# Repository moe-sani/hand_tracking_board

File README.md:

# hand_tracking_board

    branch name: backup_8_core_board
    hardware version: 
    Processor: Arduino 

* author: Mohammad Fattahi Sani
* Email: fattahi.m91@gmail.com

----------

This is the old board used to collect data using logic analyzer.

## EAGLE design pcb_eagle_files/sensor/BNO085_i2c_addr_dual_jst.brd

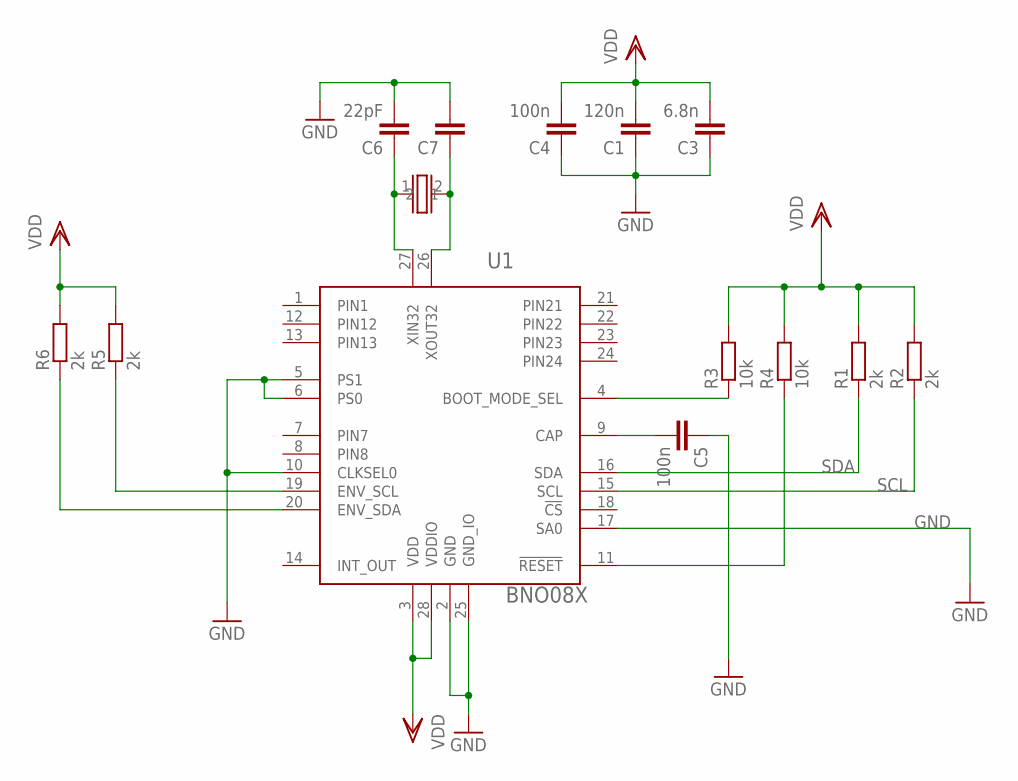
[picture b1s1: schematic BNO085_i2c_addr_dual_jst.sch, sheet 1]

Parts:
C1: 120n; C0402
C3: 6.8n; C0402
C4, C5: 100n; C0402
C6: 22pF; C0402
C7: C-EUC0402; C0402
R1, R2, R5, R6: 2k; R0402
R3, R4: 10k; R0402
U1: BNO08X; LGA-28_3.80X5.20/0.5
U$1: ABS05

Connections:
GND: C1.1, C3.1, C4.1, C5.1, C6.2, C7.2, U1.2 (GND), U1.5 (PS1), U1.6 (PS0), U1.10 (CLKSEL0), U1.17 (SA0), U1.25 (GND_IO); also elsewhere on the board
unnamed: C6.1, U1.27 (XIN32), U$1.1
unnamed: C7.1, U1.26 (XOUT32), U$1.2
unnamed: C5.2, U1.9 (CAP)
unnamed: R3.1, U1.4 (BOOT_MODE_SEL)
unnamed: R5.1, U1.19 (ENV_SCL)
unnamed: R4.1, U1.11 (!RESET)
unnamed: R6.1, U1.20 (ENV_SDA)
SCL: R2.1, U1.15 (SCL); also elsewhere on the board
SDA: R1.1, U1.16 (SDA); also elsewhere on the board
VDD: C1.2, C3.2, C4.2, R1.2, R2.2, R3.2, R4.2, R5.2, R6.2, U1.3 (VDD), U1.28 (VDDIO); also elsewhere on the board

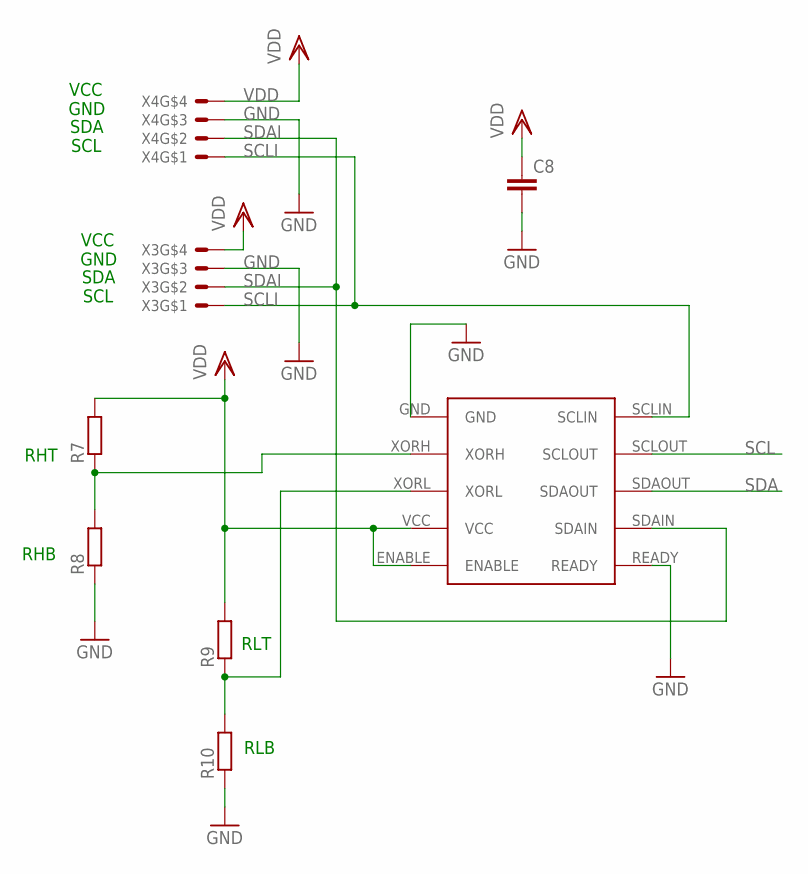
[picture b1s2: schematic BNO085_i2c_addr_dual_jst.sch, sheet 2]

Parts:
C8: C-EUC0402; C0402
R7, R8, R9, R10: R-EU_R0402; R0402
U$3: LIC4316; DD-DFN-10
X3, X4: SM04B-XSRS; SM04B-XSRS-ETB

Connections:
GND: C8.2, R8.1, R10.1, U$3.GND, U$3.READY, X3.3, X4.3; also elsewhere on the board
unnamed: R7.1, R8.2, U$3.XORH
unnamed: R9.1, R10.2, U$3.XORL
SCL: U$3.SCLOUT; also elsewhere on the board
SCLI: U$3.SCLIN, X3.1, X4.1
SDA: U$3.SDAOUT; also elsewhere on the board
SDAI: U$3.SDAIN, X3.2, X4.2
VDD: C8.1, R7.2, R9.2, U$3.ENABLE, U$3.VCC, X3.4, X4.4; also elsewhere on the board

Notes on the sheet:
SCL
SDA
VCC
GND
RHT
RHB
RLT
RLB

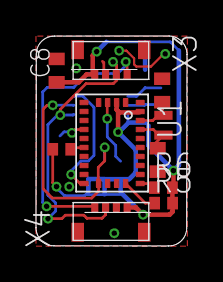
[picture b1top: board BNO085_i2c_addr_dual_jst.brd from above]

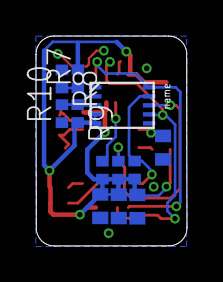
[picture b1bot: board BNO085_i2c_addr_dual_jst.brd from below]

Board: 2 copper layers, 8.4 x 11.7 mm, 24 parts (12 on the bottom side), 15 nets.

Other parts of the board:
LOGO3: OSHW-LOGOS; OSHW-LOGO-S
U$2: BQ_LOGO_MEDIUM

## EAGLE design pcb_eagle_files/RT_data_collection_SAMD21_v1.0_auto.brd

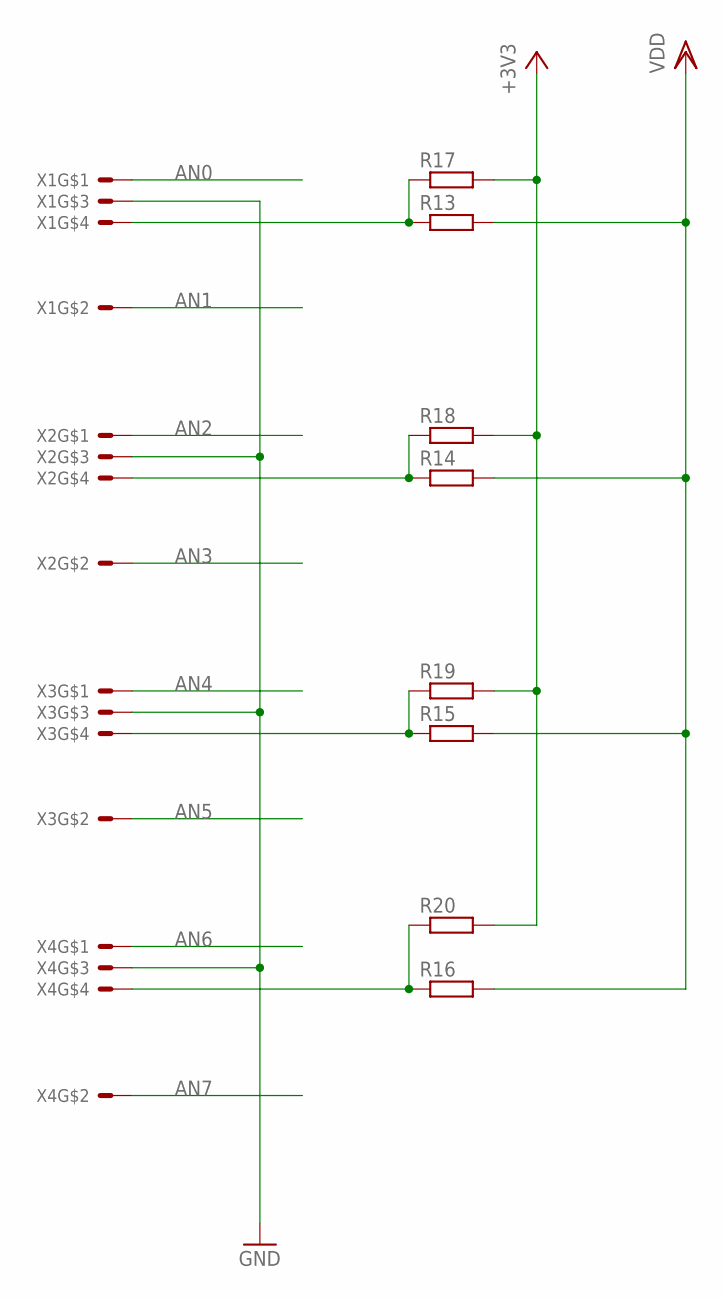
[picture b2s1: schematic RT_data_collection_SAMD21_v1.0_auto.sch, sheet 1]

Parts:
R13, R14, R15, R16, R17, R18, R19, R20: R-EU_R0201; R0201
X1, X3: CON-JST2_SM04B-XSRS; CON-JST2_SM04B-XSRS-ETB
X2, X4: SM04B-XSRS; SM04B-XSRS-ETB

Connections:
+3V3: R17.2, R18.2, R19.2, R20.2; also elsewhere on the board
AN0: X1.1; also elsewhere on the board
AN1: X1.2; also elsewhere on the board
AN2: X2.1; also elsewhere on the board
AN3: X2.2; also elsewhere on the board
AN4: X3.1; also elsewhere on the board
AN5: X3.2; also elsewhere on the board
AN6: X4.1; also elsewhere on the board
AN7: X4.2; also elsewhere on the board
GND: X1.3, X2.3, X3.3, X4.3; also elsewhere on the board
unnamed: R16.1, R20.1, X4.4
unnamed: R14.1, R18.1, X2.4
unnamed: R15.1, R19.1, X3.4
unnamed: R13.1, R17.1, X1.4
VDD: R13.2, R14.2, R15.2, R16.2; also elsewhere on the board

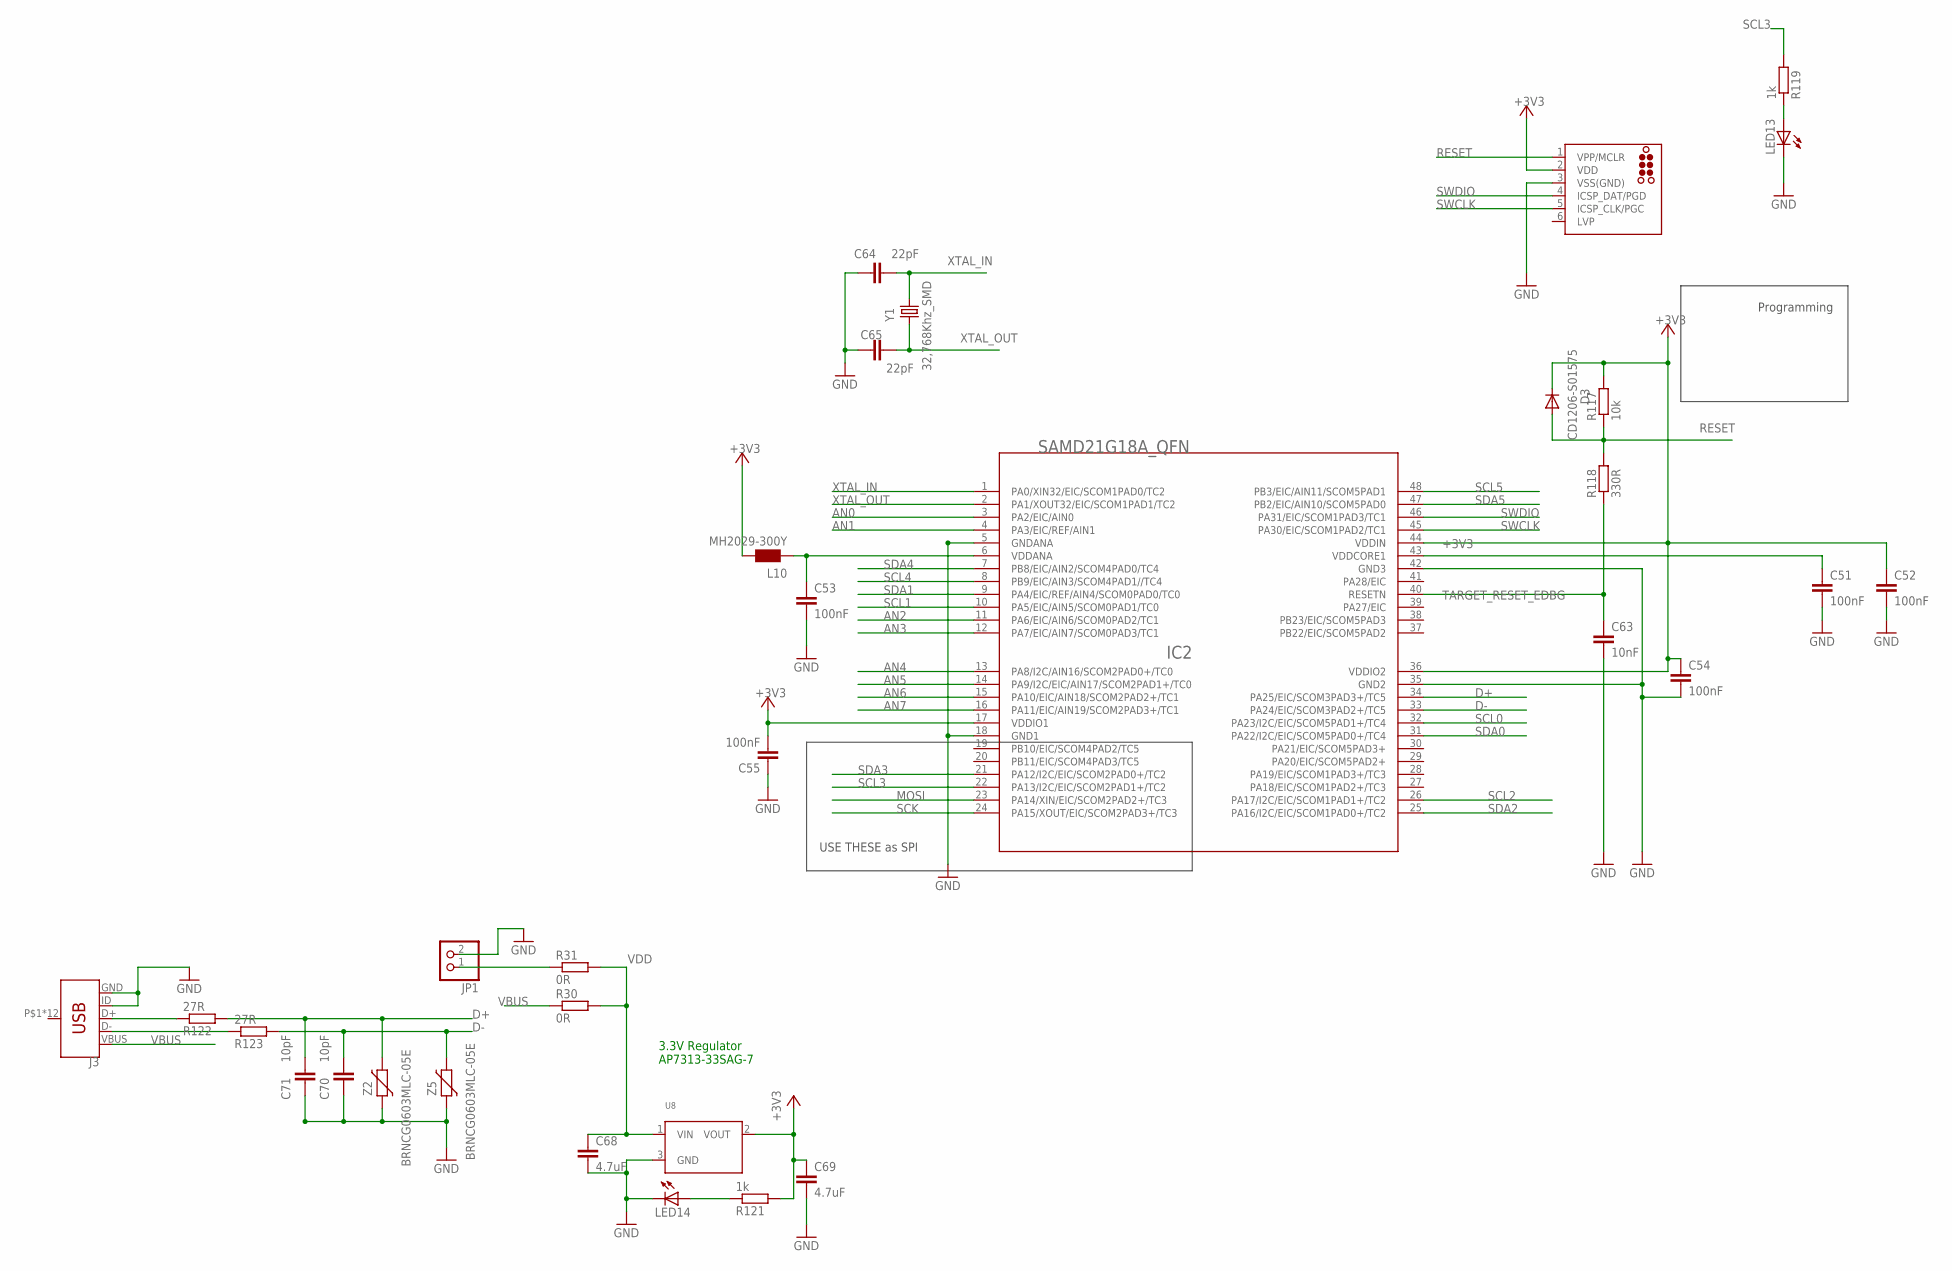
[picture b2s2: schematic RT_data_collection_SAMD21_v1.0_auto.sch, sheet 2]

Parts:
C51, C52, C53, C54, C55: 100nF; C0402
C63: 10nF; C0402
C64, C65: 22pF; C0402
C68, C69: 4.7uF; C0603
C70, C71: 10pF; C0402
D3: CD1206-S01575; MINIMELF
IC2: SAMD21G18A_QFN
J2: TC2030-MCP-NL
J3: USB_MICRO-B; USB-MICROB-PTH-WIDE
JP1: PINHD-1X2; 1X02
L10: MH2029-300Y; 0805
LED13, LED14: LEDCHIPLED_0805; CHIPLED_0805
R30, R31: 0R; R0603
R117: 10k; R0402
R118: 330R; R0402
R119, R121: 1k; R0402
R122, R123: 27R; R0402
U8: VREG_SOT23; SOT23-R
Y1: 32,768Khz_SMD; CRISTALLI_RESONATOR_EPSON_FC_145
Z2, Z5: BRNCG0603MLC-05E; CT/CN0603

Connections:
+3V3: C52.1, C54.1, C55.2, C69.1, D3.C, IC2.17 (VDDIO1), IC2.36 (VDDIO2), IC2.44 (VDDIN), J2.2 (VDD), L10.2, R117.2, R121.2, U8.2 (VOUT); also elsewhere on the board
AN0: IC2.3 (PA2/EIC/AIN0); also elsewhere on the board
AN1: IC2.4 (PA3/EIC/REF/AIN1); also elsewhere on the board
AN2: IC2.11 (PA6/EIC/AIN6/SCOM0PAD2/TC1); also elsewhere on the board
AN3: IC2.12 (PA7/EIC/AIN7/SCOM0PAD3/TC1); also elsewhere on the board
AN4: IC2.13 (PA8/I2C/AIN16/SCOM2PAD0+/TC0); also elsewhere on the board
AN5: IC2.14 (PA9/I2C/EIC/AIN17/SCOM2PAD1+/TC0); also elsewhere on the board
AN6: IC2.15 (PA10/EIC/AIN18/SCOM2PAD2+/TC1); also elsewhere on the board
AN7: IC2.16 (PA11/EIC/AIN19/SCOM2PAD3+/TC1); also elsewhere on the board
D+: C71.2, IC2.34 (PA25/EIC/SCOM3PAD3+/TC5), R122.2, Z2.2
D-: C70.2, IC2.33 (PA24/EIC/SCOM3PAD2+/TC5), R123.2, Z5.2
GND: C51.2, C52.2, C53.2, C54.2, C55.1, C63.2, C64.1, C65.1, C68.2, C69.2, C70.1, C71.1, IC2.5 (GNDANA), IC2.18 (GND1), IC2.35 (GND2), IC2.42 (GND3), J2.3 (VSS(GND)), J3.GND, J3.ID, JP1.2, LED13.C, LED14.C, U8.3 (GND), Z2.1, Z5.1; also elsewhere on the board
MOSI: IC2.23 (PA14/XIN/EIC/SCOM2PAD2+/TC3)
unnamed: J3.D+, R122.1
unnamed: J3.D-, R123.1
unnamed: C51.1, IC2.43 (VDDCORE1)
unnamed: JP1.1, R31.1
unnamed: C53.1, IC2.6 (VDDANA), L10.1
unnamed: LED13.A, R119.1
unnamed: LED14.A, R121.1
RESET: D3.A, J2.1 (VPP/MCLR), R117.1, R118.2
SCK: IC2.24 (PA15/XOUT/EIC/SCOM2PAD3+/TC3)
SCL0: IC2.32 (PA23/I2C/EIC/SCOM5PAD1+/TC4); also elsewhere on the board
SCL1: IC2.10 (PA5/EIC/AIN5/SCOM0PAD1/TC0); also elsewhere on the board
SCL2: IC2.26 (PA17/I2C/EIC/SCOM1PAD1+/TC2); also elsewhere on the board
SCL3: IC2.22 (PA13/I2C/EIC/SCOM2PAD1+/TC2), R119.2; also elsewhere on the board
SCL4: IC2.8 (PB9/EIC/AIN3/SCOM4PAD1//TC4); also elsewhere on the board
SCL5: IC2.48 (PB3/EIC/AIN11/SCOM5PAD1); also elsewhere on the board
SDA0: IC2.31 (PA22/I2C/EIC/SCOM5PAD0+/TC4); also elsewhere on the board
SDA1: IC2.9 (PA4/EIC/REF/AIN4/SCOM0PAD0/TC0); also elsewhere on the board
SDA2: IC2.25 (PA16/I2C/EIC/SCOM1PAD0+/TC2); also elsewhere on the board
SDA3: IC2.21 (PA12/I2C/EIC/SCOM2PAD0+/TC2); also elsewhere on the board
SDA4: IC2.7 (PB8/EIC/AIN2/SCOM4PAD0/TC4); also elsewhere on the board
SDA5: IC2.47 (PB2/EIC/AIN10/SCOM5PAD0); also elsewhere on the board
SWCLK: IC2.45 (PA30/EIC/SCOM1PAD2/TC1), J2.5 (ICSP_CLK/PGC)
SWDIO: IC2.46 (PA31/EIC/SCOM1PAD3/TC1), J2.4 (ICSP_DAT/PGD)
TARGET_RESET_EDBG: C63.1, IC2.40 (RESETN), R118.1
VBUS: J3.VBUS, R30.1
VDD: C68.1, R30.2, R31.2, U8.1 (VIN); also elsewhere on the board
XTAL_IN: C64.2, IC2.1 (PA0/XIN32/EIC/SCOM1PAD0/TC2), Y1.P$2 (2)
XTAL_OUT: C65.2, IC2.2 (PA1/XOUT32/EIC/SCOM1PAD1/TC2), Y1.P$1 (1)

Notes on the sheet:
3.3V Regulator AP7313-33SAG-7
USE THESE as SPI
Programming

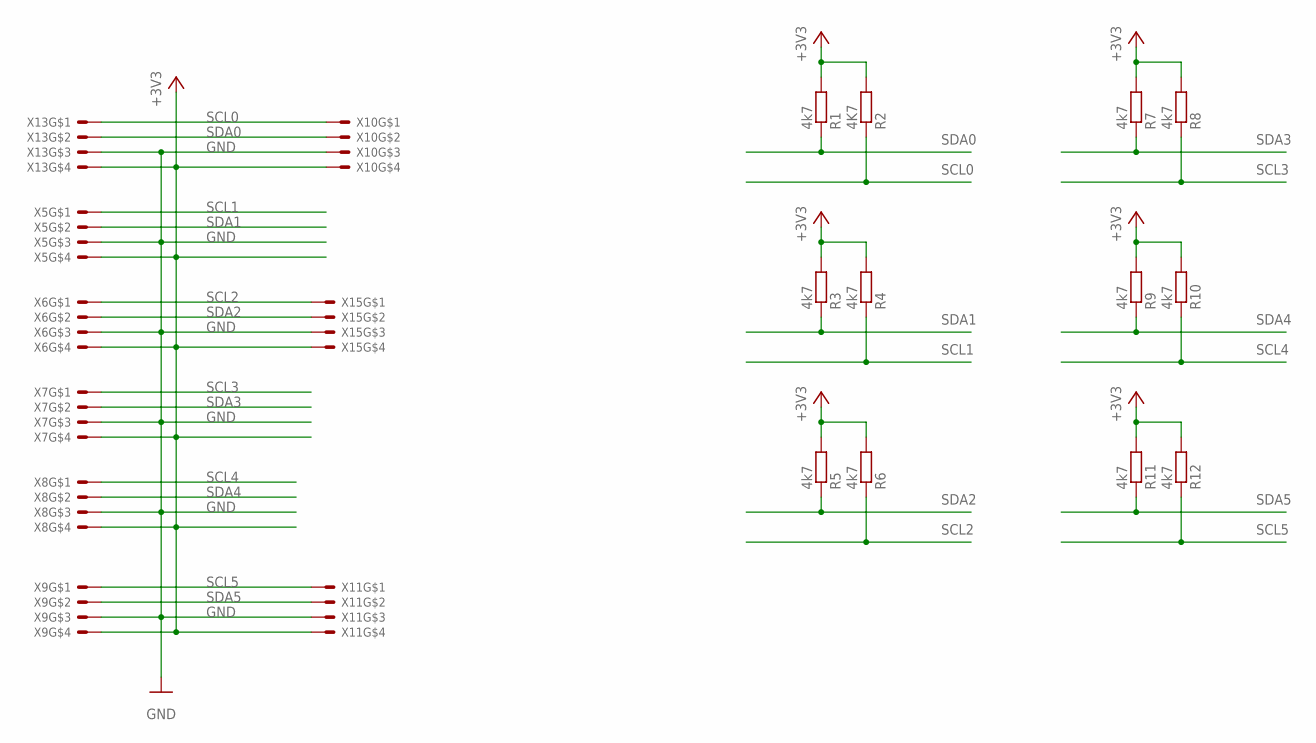
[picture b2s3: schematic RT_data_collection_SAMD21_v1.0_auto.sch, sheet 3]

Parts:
R1, R3, R4, R5, R6, R7, R8, R9, R10, R11, R12: 4k7; R0402
R2: 4K7; R0402
X5, X6, X7, X8, X9, X10, X11, X13, X15: SM04B-XSRS; SM04B-XSRS-ETB

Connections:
+3V3: R1.2, R2.2, R3.2, R4.2, R5.2, R6.2, R7.2, R8.2, R9.2, R10.2, R11.2, R12.2, X5.4, X6.4, X7.4, X8.4, X9.4, X10.4, X11.4, X13.4, X15.4; also elsewhere on the board
GND: X5.3, X6.3, X7.3, X8.3, X9.3, X10.3, X11.3, X13.3, X15.3; also elsewhere on the board
SCL0: R2.1, X10.1, X13.1; also elsewhere on the board
SCL1: R4.1, X5.1; also elsewhere on the board
SCL2: R6.1, X6.1, X15.1; also elsewhere on the board
SCL3: R8.1, X7.1; also elsewhere on the board
SCL4: R10.1, X8.1; also elsewhere on the board
SCL5: R12.1, X9.1, X11.1; also elsewhere on the board
SDA0: R1.1, X10.2, X13.2; also elsewhere on the board
SDA1: R3.1, X5.2; also elsewhere on the board
SDA2: R5.1, X6.2, X15.2; also elsewhere on the board
SDA3: R7.1, X7.2; also elsewhere on the board
SDA4: R9.1, X8.2; also elsewhere on the board
SDA5: R11.1, X9.2, X11.2; also elsewhere on the board

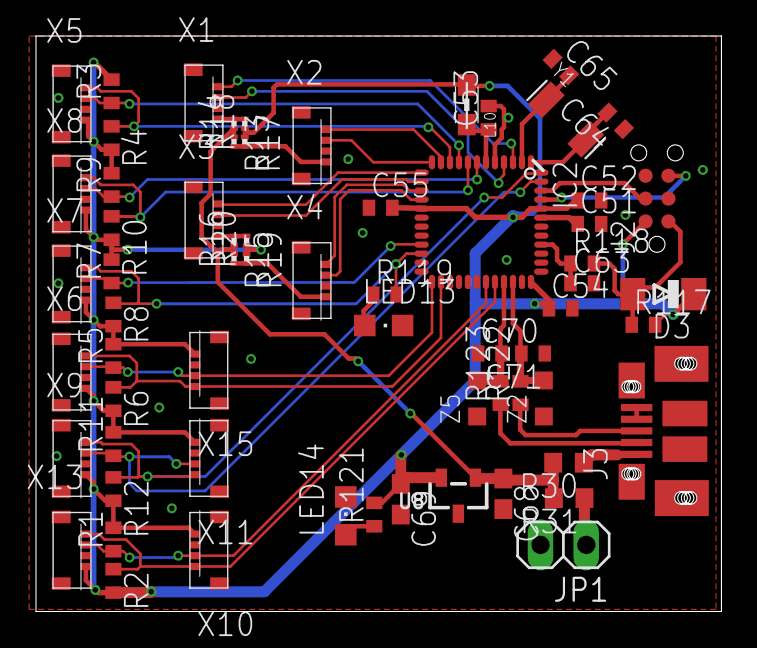
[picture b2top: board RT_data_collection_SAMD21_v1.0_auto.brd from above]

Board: 2 copper layers, 38.1 x 32.0 mm, 65 parts (0 on the bottom side), 43 nets.

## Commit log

2019-07-15 Update README.md
    first readme
2019-07-23 i dont know
2019-07-29 add isConnected bit to class
2019-07-29 fixed isconnected+ send calibration values through the serial
2019-08-20 code working for BNOo80, but it needs more cleaning
2019-08-21 supprts BNO055 and 080 automaticly!
2019-08-23 this commit breaks a lot! it messes up the serial strings
2019-10-02 final one, not sure what
2019-10-05 first proper version for the red board with BNO080
2019-10-07 idont know
2019-10-07 channel 0 works well with bno055
2019-10-07 still only works for first i2c
2019-10-08 trying to find problem why wire2 doesnt work!
2019-10-10 getting ready to give to cyx
2019-10-18 version tested with CYX
2019-10-18 added ai2c check loop
2019-10-22 small modifications to make it similar to cyx board
2019-10-28 add readme + calibration values
2019-11-25 added 3 more sensors
2019-11-27 updated the readme
2019-11-28 added pcb files (not the final versions)
2021-10-25 Create LICENSE

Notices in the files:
parts and their libraries:
2mm connector: This work is placed in the public domain, and may be freely used for commercial and non-commercial work with the following conditions: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
tag-connect: ©2009 ROFA.cz - modified and updated by Robert Darlington ‹rdarlington@gmail.com›
